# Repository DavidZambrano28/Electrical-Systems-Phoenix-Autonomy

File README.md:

# FPU RoboBoat Electrical Systems

This repo board contains all firmware and electronics for power delivery, ESC commanding, and LoRa interfacing for a robust electrical system.

## Mina Board Features:

**Power Delivery:**

12V, 15V, 5V rails. Powers everything on the boat (LiDar, Jetson Nano, etc).

**Remote & On-board E-stop:**

LoRa module & the Big Red Button (BRB) plugs into the board via JST-XH connector, interfaces with Pi Pico. Pi Pico controls the optocoupler LED. 

The Pico will run a simple if statement, only when the BRB isn't pressed & the LoRa module isn't sending an open command will the Pico turn on the optocoupler LED, closing the contactor. In this configuration, the Pico is holding the contactor closed, meaning if power is lost for any reason the contactor defaults to being open.

The board will also include a "READY" LED and a "INDICATOR" LED, the former only being on when the contactor is closed and the latter providing status updates.

**Thruster Control**

The Pico will also interface and command the thruster ESC via a JST-XH connector. Commands to the Pico will be gathered over serial via the RX pin from either the FlySky transmitter or the Jetson Nano.

## Contributors

- [David Zambrano] - [@TheDogIsHungry](https://github.com/TheDogIsHungry)
- [Nerlin Charles] - [@NCharles101](https://github.com/NCharles101)
- [Gabriel Morgan] - [@GMorgan2776](https://github.com/GMorgan2776)
- [Ivan Domi]      - [@idomi17](https://github.com/idomi17)

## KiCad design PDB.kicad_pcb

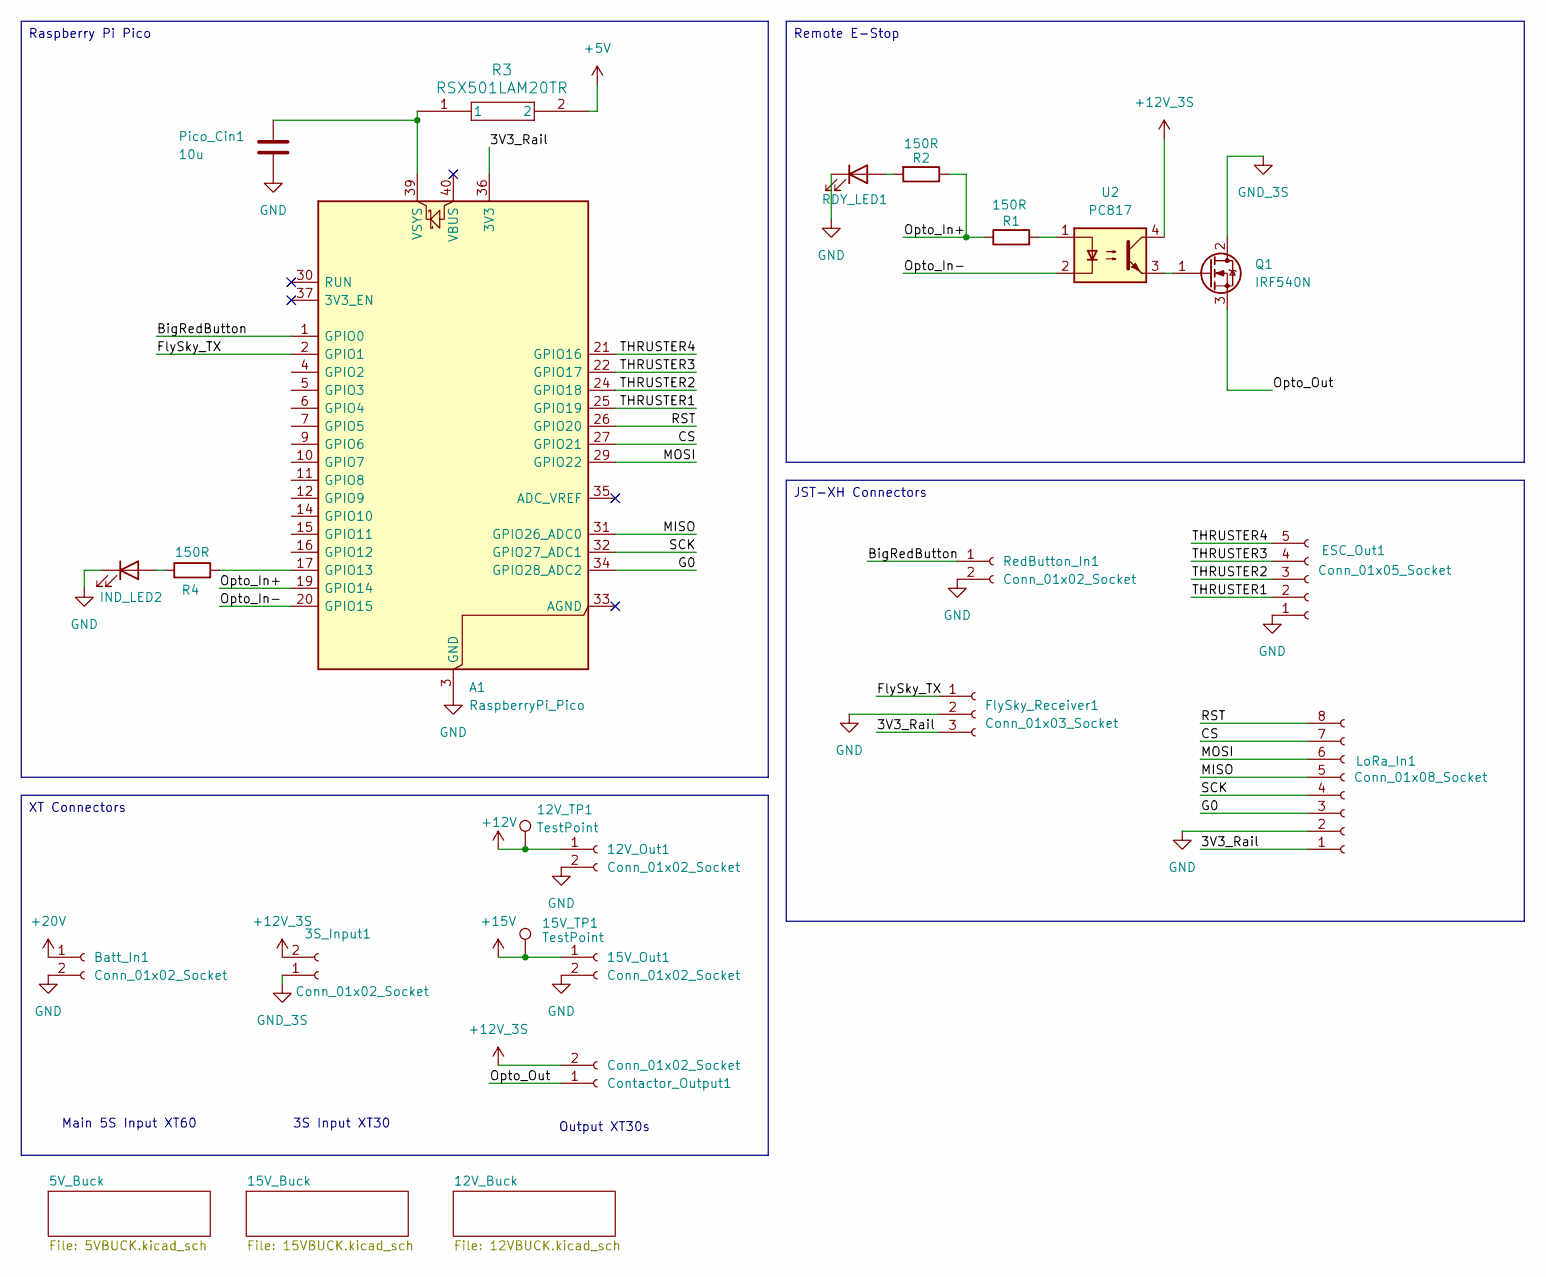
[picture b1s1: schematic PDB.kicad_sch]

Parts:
3S_Input1: Conn_01x02_Socket; AMASS_XT30U-M_1x02_P5.0mm_Vertical
12V_Out1, 15V_Out1: Conn_01x02_Socket; AMASS_XT30U-F_1x02_P5.0mm_Vertical
12V_TP1, 15V_TP1: TestPoint; TestPoint_Pad_D2.0mm
A1: RaspberryPi_Pico; RaspberryPi_Pico_Common_THT
Batt_In1: Conn_01x02_Socket; AMASS_XT60-M_1x02_P7.20mm_Vertical
Contactor_Output1: Conn_01x02_Socket; AMASS_XT30U-F_1x02_P5.0mm_Vertical
ESC_Out1: Conn_01x05_Socket; JST_XH_B5B-XH-A_1x05_P2.50mm_Vertical
FlySky_Receiver1: Conn_01x03_Socket; JST_XH_B3B-XH-A_1x03_P2.50mm_Vertical
IND_LED2: LED; LED_D5.0mm
LoRa_In1: Conn_01x08_Socket; JST_XH_B8B-XH-A_1x08_P2.50mm_Vertical
Pico_Cin1: 10u; C_0805_2012Metric
Q1: IRF540N; TO-220-3_Vertical
R1, R2, R4: 150R; R_0805_2012Metric
R3: RSX501LAM20TR; DIO_RB050LAM_ROM
RDY_LED1: LED; LED_D5.0mm
RedButton_In1: Conn_01x02_Socket; JST_XH_B2B-XH-A_1x02_P2.50mm_Vertical
U2: PC817; DIP-4_W7.62mm

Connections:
+5V: R3.2; also elsewhere on the board
+12V: 12V_Out1.1, 12V_TP1.1 (1_1); also elsewhere on the board
+12V_3S: 3S_Input1.2, Contactor_Output1.2, U2.4
+15V: 15V_Out1.1, 15V_TP1.1 (1_1); also elsewhere on the board
+20V: Batt_In1.1; also elsewhere on the board
/3V3_Rail: A1.36 (3V3), FlySky_Receiver1.3, LoRa_In1.1
/BigRedButton: A1.1 (GPIO0), RedButton_In1.1
/CS: A1.27 (GPIO21), LoRa_In1.7
/FlySky_TX: A1.2 (GPIO1), FlySky_Receiver1.1
/G0: A1.34 (GPIO28_ADC2), LoRa_In1.3
/MISO: A1.31 (GPIO26_ADC0), LoRa_In1.5
/MOSI: A1.29 (GPIO22), LoRa_In1.6
/Opto_In+: A1.19 (GPIO14), R1.1, R2.1
/Opto_In-: A1.20 (GPIO15), U2.2
/Opto_Out: Contactor_Output1.1, Q1.3 (S)
/RST: A1.26 (GPIO20), LoRa_In1.8
/SCK: A1.32 (GPIO27_ADC1), LoRa_In1.4
/THRUSTER1: A1.25 (GPIO19), ESC_Out1.2
/THRUSTER2: A1.24 (GPIO18), ESC_Out1.3
/THRUSTER3: A1.22 (GPIO17), ESC_Out1.4
/THRUSTER4: A1.21 (GPIO16), ESC_Out1.5
GND: 12V_Out1.2, 15V_Out1.2, A1.3 (GND), A1.8 (GND), A1.13 (GND), A1.18 (GND), A1.23 (GND), A1.28 (GND), A1.38 (GND), Batt_In1.2, ESC_Out1.1, FlySky_Receiver1.2, IND_LED2.1 (K), LoRa_In1.2, Pico_Cin1.2, RDY_LED1.1 (K), RedButton_In1.2; also elsewhere on the board
GND_3S: 3S_Input1.1, Q1.2 (D)
unnamed: A1.17 (GPIO13), R4.2
unnamed: A1.39 (VSYS), Pico_Cin1.1, R3.1
unnamed: IND_LED2.2 (A), R4.1
unnamed: Q1.1 (G), U2.3
unnamed: R1.2, U2.1
unnamed: R2.2, RDY_LED1.2 (A)

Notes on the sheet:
Main 5S Input XT60
Output XT30s
3S Input XT30
Raspberry Pi Pico
XT Connectors
Remote E-Stop
JST-XH Connectors

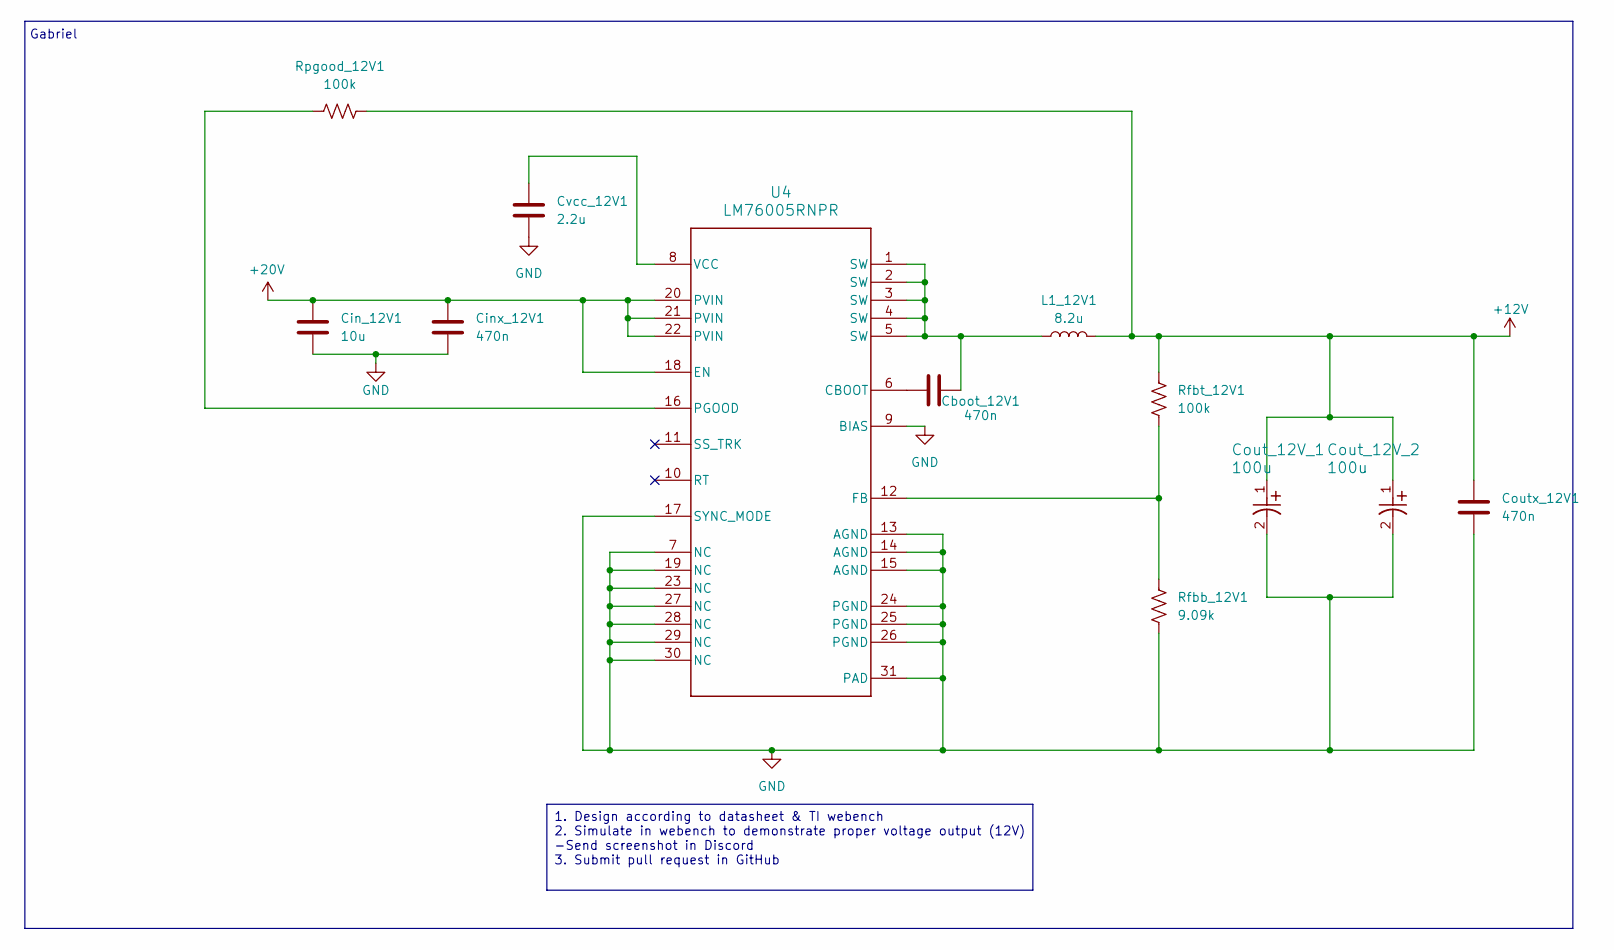
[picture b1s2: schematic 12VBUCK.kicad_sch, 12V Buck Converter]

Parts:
Cboot_12V1: 470n; C_0805_2012Metric
Cin_12V1: 10u; C_0805_2012Metric
Cinx_12V1: 470n; C_0805_2012Metric
Cout_12V_1, Cout_12V_2: 100u; CAP_EEFK_F_PAN
Coutx_12V1: 470n; C_0805_2012Metric
Cvcc_12V1: 2.2u; C_0603_1608Metric
L1_12V1: 8.2u; L_Bourns_SRP7028A_7.3x6.6mm
Rfbb_12V1: 9.09k; R_0603_1608Metric
Rfbt_12V1: 100k; R_0603_1608Metric
Rpgood_12V1: 100k; R_0603_1608Metric
U4: LM76005RNPR; RNP0030A

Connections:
+12V: Cout_12V_1.1, Cout_12V_2.1, Coutx_12V1.1, L1_12V1.2, Rfbt_12V1.2, Rpgood_12V1.2; also elsewhere on the board
+20V: Cin_12V1.1, Cinx_12V1.1, U4.18 (EN), U4.20 (PVIN), U4.21 (PVIN), U4.22 (PVIN); also elsewhere on the board
GND: Cin_12V1.2, Cinx_12V1.2, Cout_12V_1.2, Cout_12V_2.2, Coutx_12V1.2, Cvcc_12V1.2, Rfbb_12V1.1, U4.7 (NC), U4.9 (BIAS), U4.13 (AGND), U4.14 (AGND), U4.15 (AGND), U4.17 (SYNC_MODE), U4.19 (NC), U4.23 (NC), U4.24 (PGND), U4.25 (PGND), U4.26 (PGND), U4.27 (NC), U4.28 (NC), U4.29 (NC), U4.30 (NC), U4.31 (PAD); also elsewhere on the board
unnamed: Cboot_12V1.1, L1_12V1.1, U4.1 (SW), U4.2 (SW), U4.3 (SW), U4.4 (SW), U4.5 (SW)
unnamed: Cboot_12V1.2, U4.6 (CBOOT)
unnamed: Rfbb_12V1.2, Rfbt_12V1.1, U4.12 (FB)
unnamed: Rpgood_12V1.1, U4.16 (PGOOD)
unnamed: Cvcc_12V1.1, U4.8 (VCC)

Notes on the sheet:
Gabriel
1. Design according to datasheet & TI webench 2. Simulate in webench to demonstrate proper voltage output (12V) -Send screenshot in Discord 3. Submit pull request in GitHub

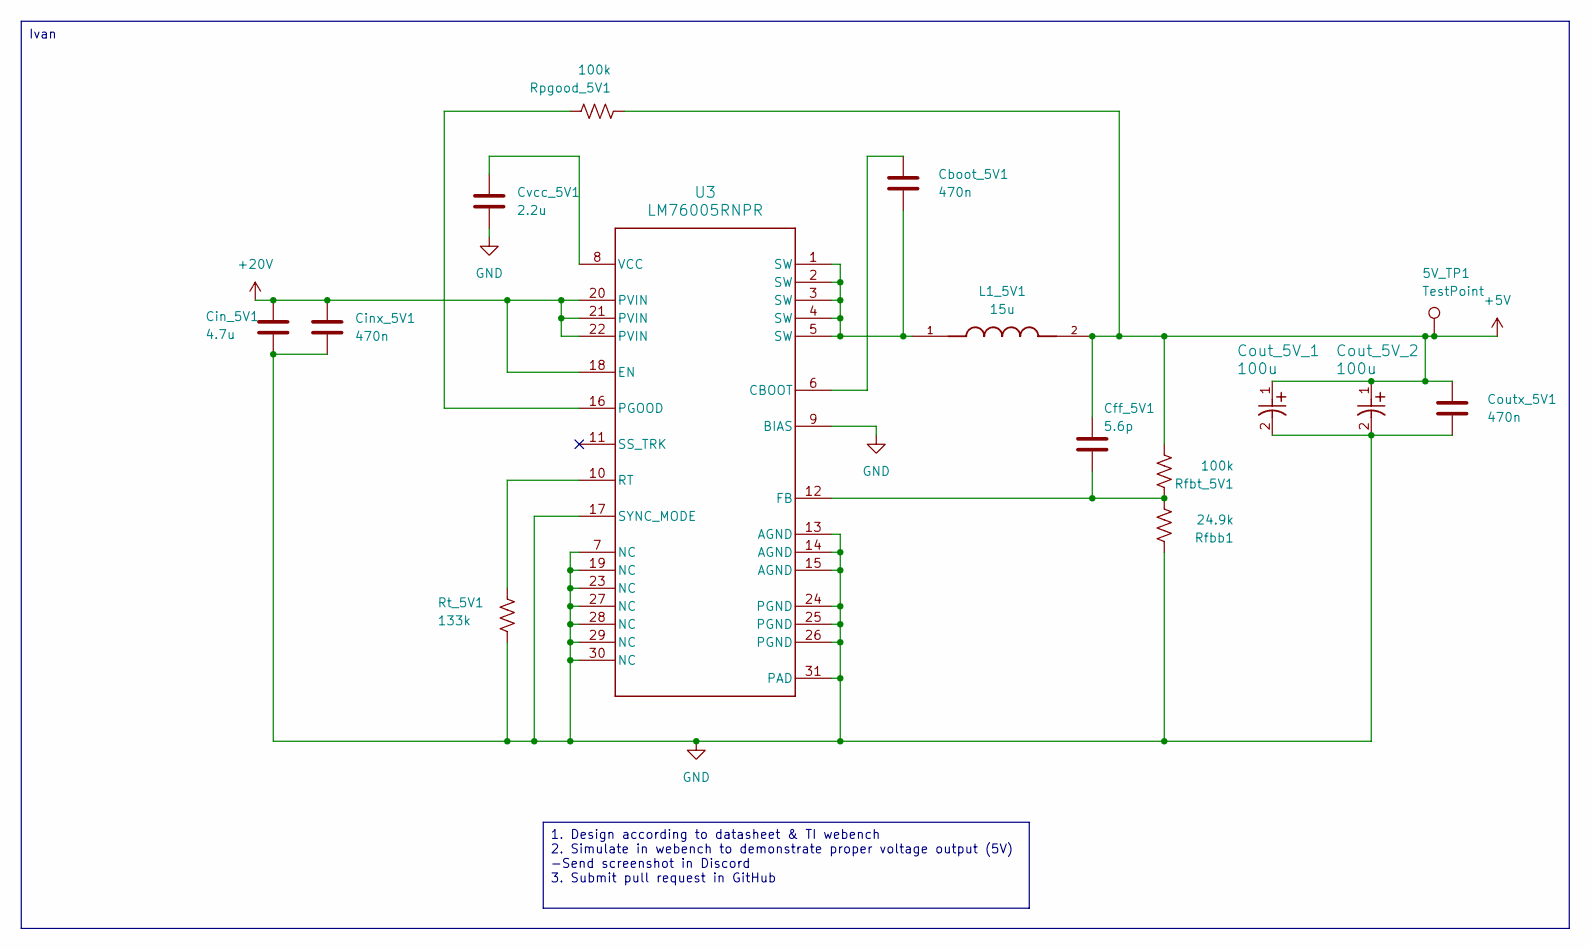
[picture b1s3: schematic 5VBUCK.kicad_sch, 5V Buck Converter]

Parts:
5V_TP1: TestPoint; TestPoint_Pad_D2.0mm
Cboot_5V1: 470n; C_0805_2012Metric
Cff_5V1: 5.6p; C_0603_1608Metric
Cin_5V1: 4.7u; C_0805_2012Metric
Cinx_5V1: 470n; C_0805_2012Metric
Cout_5V_1, Cout_5V_2: 100u; CAP_EEFK_F_PAN
Coutx_5V1: 470n; C_0805_2012Metric
Cvcc_5V1: 2.2u; C_0603_1608Metric
L1_5V1: 15u; IND_1217AS-H-150M=P3; PARTREV N/A
Rfbb1: 24.9k; R_0603_1608Metric
Rfbt_5V1: 100k; R_0603_1608Metric
Rpgood_5V1: 100k; R_0603_1608Metric
Rt_5V1: 133k; R_0603_1608Metric
U3: LM76005RNPR; RNP0030A

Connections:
+5V: 5V_TP1.1 (1_1), Cff_5V1.1, Cout_5V_1.1, Cout_5V_2.1, Coutx_5V1.1, L1_5V1.2, Rfbt_5V1.2, Rpgood_5V1.2; also elsewhere on the board
+20V: Cin_5V1.1, Cinx_5V1.1, U3.18 (EN), U3.20 (PVIN), U3.21 (PVIN), U3.22 (PVIN); also elsewhere on the board
GND: Cin_5V1.2, Cinx_5V1.2, Cout_5V_1.2, Cout_5V_2.2, Coutx_5V1.2, Cvcc_5V1.2, Rfbb1.1, Rt_5V1.2, U3.7 (NC), U3.9 (BIAS), U3.13 (AGND), U3.14 (AGND), U3.15 (AGND), U3.17 (SYNC_MODE), U3.19 (NC), U3.23 (NC), U3.24 (PGND), U3.25 (PGND), U3.26 (PGND), U3.27 (NC), U3.28 (NC), U3.29 (NC), U3.30 (NC), U3.31 (PAD); also elsewhere on the board
unnamed: Cboot_5V1.2, L1_5V1.1, U3.1 (SW), U3.2 (SW), U3.3 (SW), U3.4 (SW), U3.5 (SW)
unnamed: Cboot_5V1.1, U3.6 (CBOOT)
unnamed: Cff_5V1.2, Rfbb1.2, Rfbt_5V1.1, U3.12 (FB)
unnamed: Rpgood_5V1.1, U3.16 (PGOOD)
unnamed: Rt_5V1.1, U3.10 (RT)
unnamed: Cvcc_5V1.1, U3.8 (VCC)

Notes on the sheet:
Ivan
1. Design according to datasheet & TI webench 2. Simulate in webench to demonstrate proper voltage output (5V) -Send screenshot in Discord 3. Submit pull request in GitHub

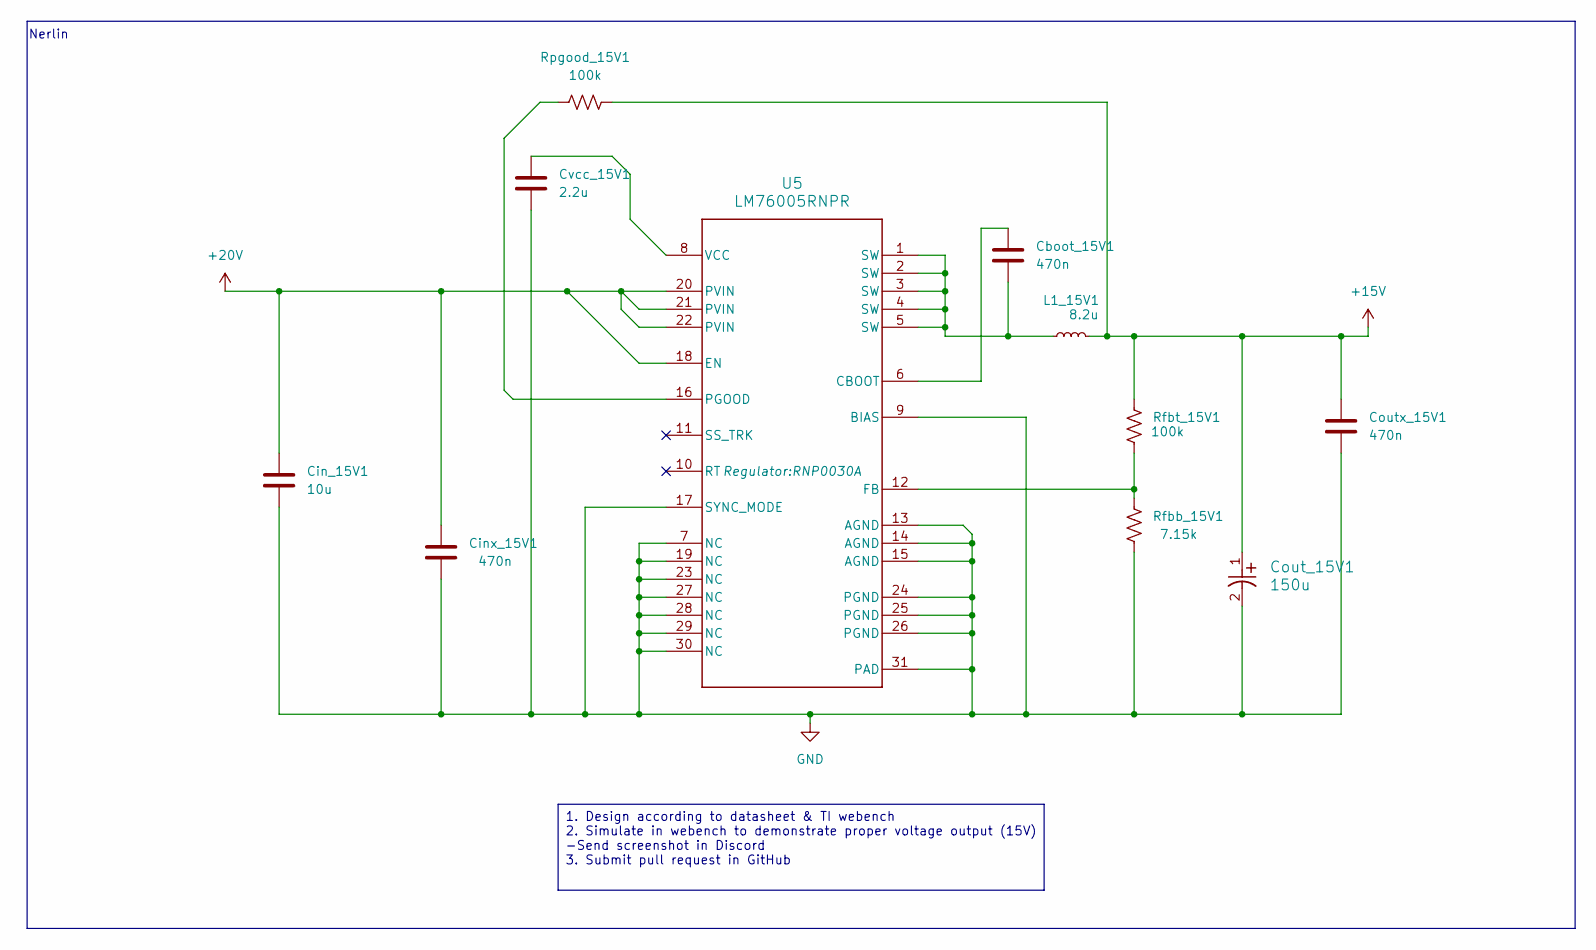
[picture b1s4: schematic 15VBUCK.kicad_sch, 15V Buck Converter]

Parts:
Cboot_15V1: 470n; C_0805_2012Metric
Cin_15V1: 10u; C_0805_2012Metric
Cinx_15V1: 470n; C_0805_2012Metric
Cout_15V1: 150u; CAP_EEFK_F_PAN
Coutx_15V1: 470n; C_0805_2012Metric
Cvcc_15V1: 2.2u; C_0603_1608Metric
L1_15V1: 8.2u; L_Bourns_SRP7028A_7.3x6.6mm
Rfbb_15V1: 7.15k; R_0603_1608Metric
Rfbt_15V1: 100k; R_0603_1608Metric
Rpgood_15V1: 100k; R_0603_1608Metric
U5: LM76005RNPR; RNP0030A

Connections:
+15V: Cout_15V1.1, Coutx_15V1.1, L1_15V1.2, Rfbt_15V1.2, Rpgood_15V1.2; also elsewhere on the board
+20V: Cin_15V1.1, Cinx_15V1.1, U5.18 (EN), U5.20 (PVIN), U5.21 (PVIN), U5.22 (PVIN); also elsewhere on the board
GND: Cin_15V1.2, Cinx_15V1.2, Cout_15V1.2, Coutx_15V1.2, Cvcc_15V1.2, Rfbb_15V1.1, U5.7 (NC), U5.9 (BIAS), U5.13 (AGND), U5.14 (AGND), U5.15 (AGND), U5.17 (SYNC_MODE), U5.19 (NC), U5.23 (NC), U5.24 (PGND), U5.25 (PGND), U5.26 (PGND), U5.27 (NC), U5.28 (NC), U5.29 (NC), U5.30 (NC), U5.31 (PAD), U5.32, U5.33, U5.34, U5.35, U5.36, U5.37, U5.38, U5.39, U5.40, U5.41, U5.42; also elsewhere on the board
unnamed: Cboot_15V1.2, L1_15V1.1, U5.1 (SW), U5.2 (SW), U5.3 (SW), U5.4 (SW), U5.5 (SW)
unnamed: Cboot_15V1.1, U5.6 (CBOOT)
unnamed: Rfbb_15V1.2, Rfbt_15V1.1, U5.12 (FB)
unnamed: Rpgood_15V1.1, U5.16 (PGOOD)
unnamed: Cvcc_15V1.1, U5.8 (VCC)

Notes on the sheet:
Nerlin
1. Design according to datasheet & TI webench 2. Simulate in webench to demonstrate proper voltage output (15V) -Send screenshot in Discord 3. Submit pull request in GitHub

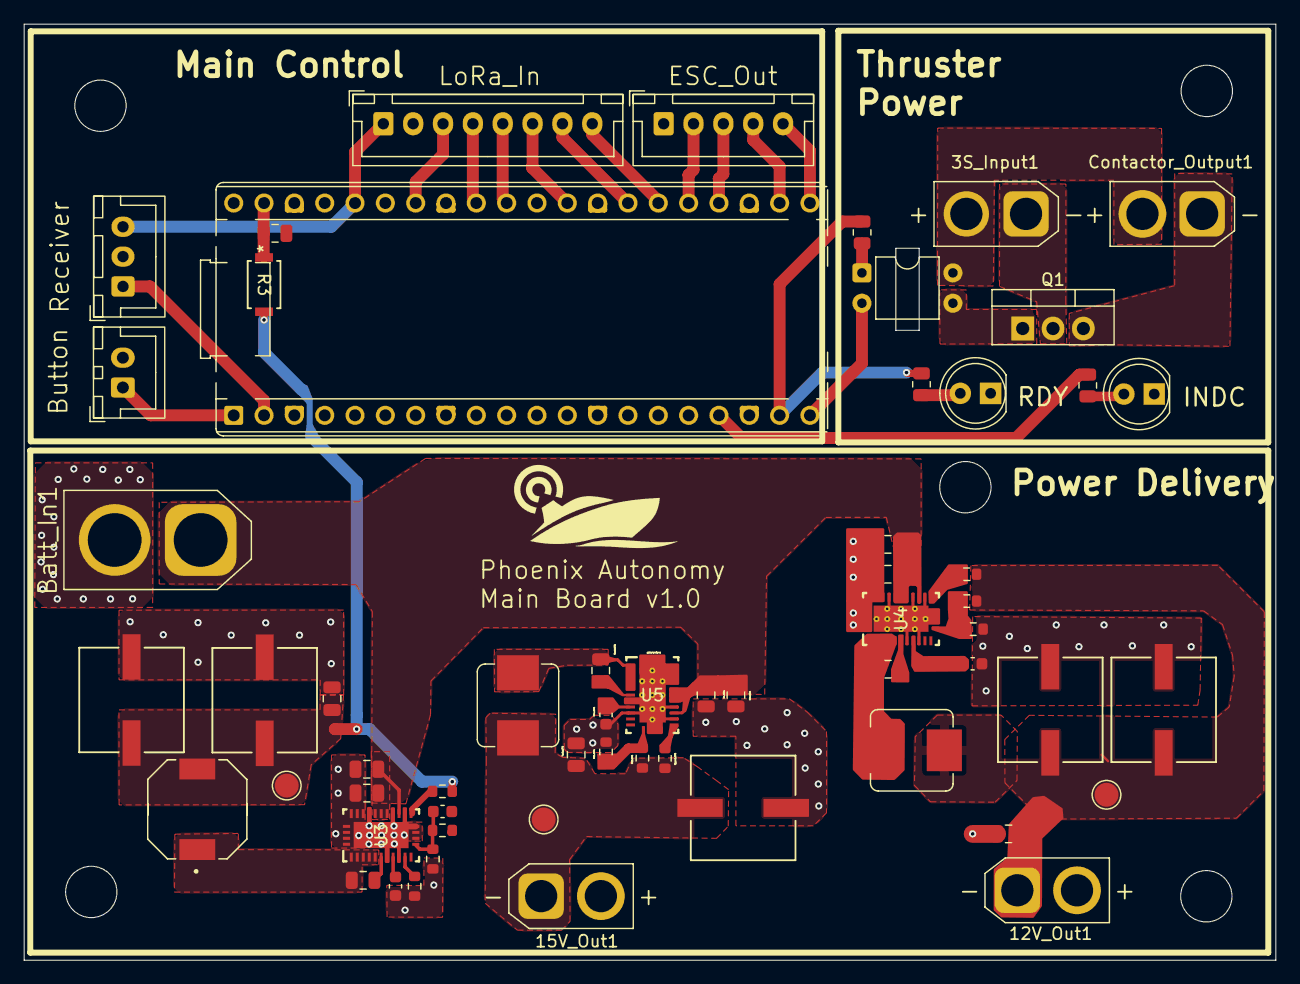
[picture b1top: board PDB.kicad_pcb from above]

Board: 4 copper layers, 104.8 x 78.4 mm, 59 parts (0 on the bottom side), 45 nets.
